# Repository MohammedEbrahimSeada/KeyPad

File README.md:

# M.Seada KeyPad

### Descirption

A personal KeyPad designed to easily use my computer in daily use with pretty design to put beside my PC, I would use it to access Copy, paste, Screenshot and Task Mgr.

### Specifications

BOM:
- 1x 0.91" 128x32 OLED Display
- 4x Cherry MX Switches
- 4x SK6812 MINI Leds
- 1x XIAO RP2040
- 4x Blank DSA Keycaps
- 4x M3x16 Bolt
- 4x M3 Heatset

Schematic            |  PCB         |   Case
:-------------------------:|:-------------------------:|:-------------------------:|
  |    |

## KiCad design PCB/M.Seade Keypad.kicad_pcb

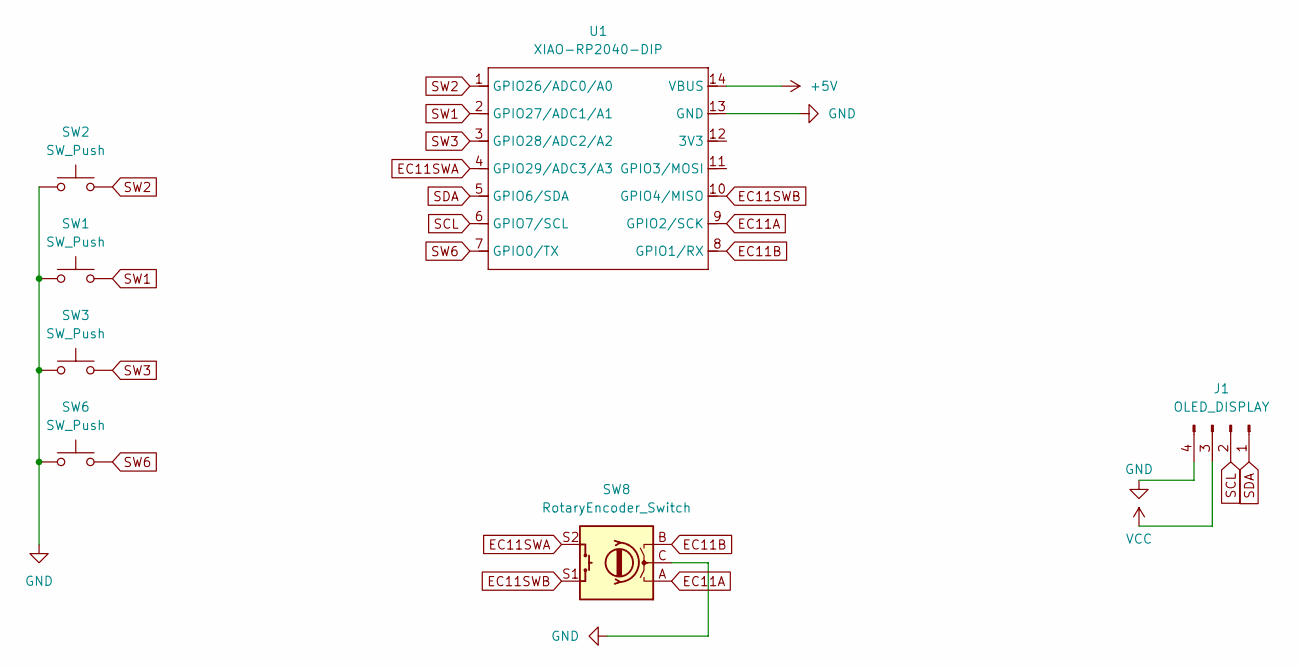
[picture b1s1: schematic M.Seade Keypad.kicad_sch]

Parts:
J1: OLED_DISPLAY; PinHeader_1x04_P2.54mm_Vertical
SW1, SW2, SW3, SW6: SW_Push; SW_Cherry_MX_1.00u_PCB
SW8: RotaryEncoder_Switch; RotaryEncoder_Alps_EC11E-Switch_Vertical_H20mm
U1: XIAO-RP2040-DIP

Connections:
+5V: U1.14 (VBUS)
EC11A: SW8.A, U1.9 (GPIO2/SCK)
EC11B: SW8.B, U1.8 (GPIO1/RX)
EC11SWA: SW8.S2, U1.4 (GPIO29/ADC3/A3)
EC11SWB: SW8.S1, U1.10 (GPIO4/MISO)
GND: J1.4, SW1.1, SW2.1, SW3.1, SW6.1, SW8.C, U1.13 (GND)
SCL: J1.2, U1.6 (GPIO7/SCL)
SDA: J1.1, U1.5 (GPIO6/SDA)
SW1: SW1.2, U1.2 (GPIO27/ADC1/A1)
SW2: SW2.2, U1.1 (GPIO26/ADC0/A0)
SW3: SW3.2, U1.3 (GPIO28/ADC2/A2)
SW6: SW6.2, U1.7 (GPIO0/TX)
VCC: J1.3

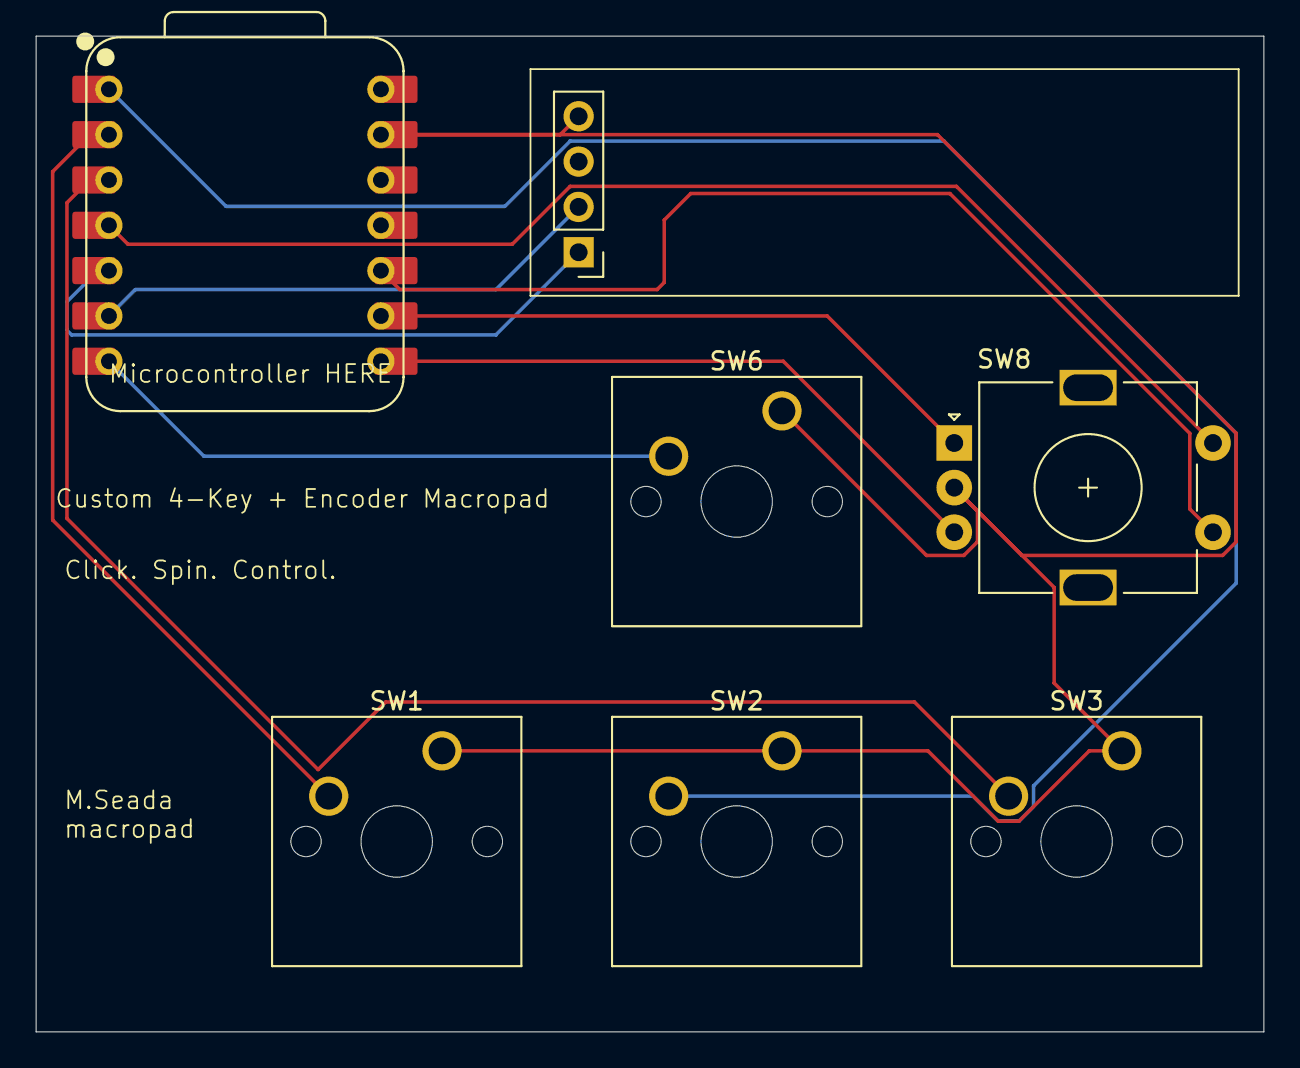
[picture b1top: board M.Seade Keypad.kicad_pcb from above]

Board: 2 copper layers, 68.8 x 55.8 mm, 7 parts (0 on the bottom side), 11 nets.
